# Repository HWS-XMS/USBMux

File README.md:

# USBMux

USB multiplexer for switching a USB device between two hosts, with VBUS power control.

## Hardware

- **MCU**: STM32F042F4P6 (USB CDC interface)
- **USB Mux**: FSUSB42MUX
- **VBUS Switch**: 2x TPS2051CDBV (with overcurrent/thermal protection)

KiCad design files in `hardware/`.

## Firmware

### Build

```bash
cd firmware
git submodule update --init --recursive
# Apply libopencm3 fix for STM32F042 USB bug
cd libopencm3 && patch -p1 < ../libopencm3-stm32f042-usb-fix.patch && cd ..
make -C libopencm3 TARGETS="stm32/f0" -j$(nproc)
make
```

**Note**: The patch fixes a critical bug in libopencm3's `st_usbfs_copy_from_pm()` function that causes data corruption when receiving odd-length USB packets on STM32F042. This bug has been reported to the libopencm3 project.

### Flash

```bash
make flash    # via ST-Link
make program  # via DFU mode
```

### Commands (USB CDC)

| Command | Description |
|---------|-------------|
| `SEL 0` / `SEL 1` | Select host 0 or 1 |
| `SEL?` | Query selection |
| `OE 0` / `OE 1` | Disable/enable mux |
| `OE?` | Query mux enable |
| `EN0 0` / `EN0 1` | Disable/enable VBUS channel 0 |
| `EN0?` | Query VBUS 0 |
| `EN1 0` / `EN1 1` | Disable/enable VBUS channel 1 |
| `EN1?` | Query VBUS 1 |
| `FAULT?` | Query fault flags |
| `STATUS?` | Query all states |

Responses end with `\r\n`.

## Software

Python wrapper in `software/usbmux.py`.

```python
from usbmux import USBMux

with USBMux() as mux:      # auto-detects device
    mux.sel = 0            # select host 0
    mux.oe = True          # enable mux
    mux.en0 = True         # enable VBUS 0 (raises USBMuxFaultError on fault)
    print(mux.status)
```

Requires `pyserial`:
```bash
pip install pyserial
```

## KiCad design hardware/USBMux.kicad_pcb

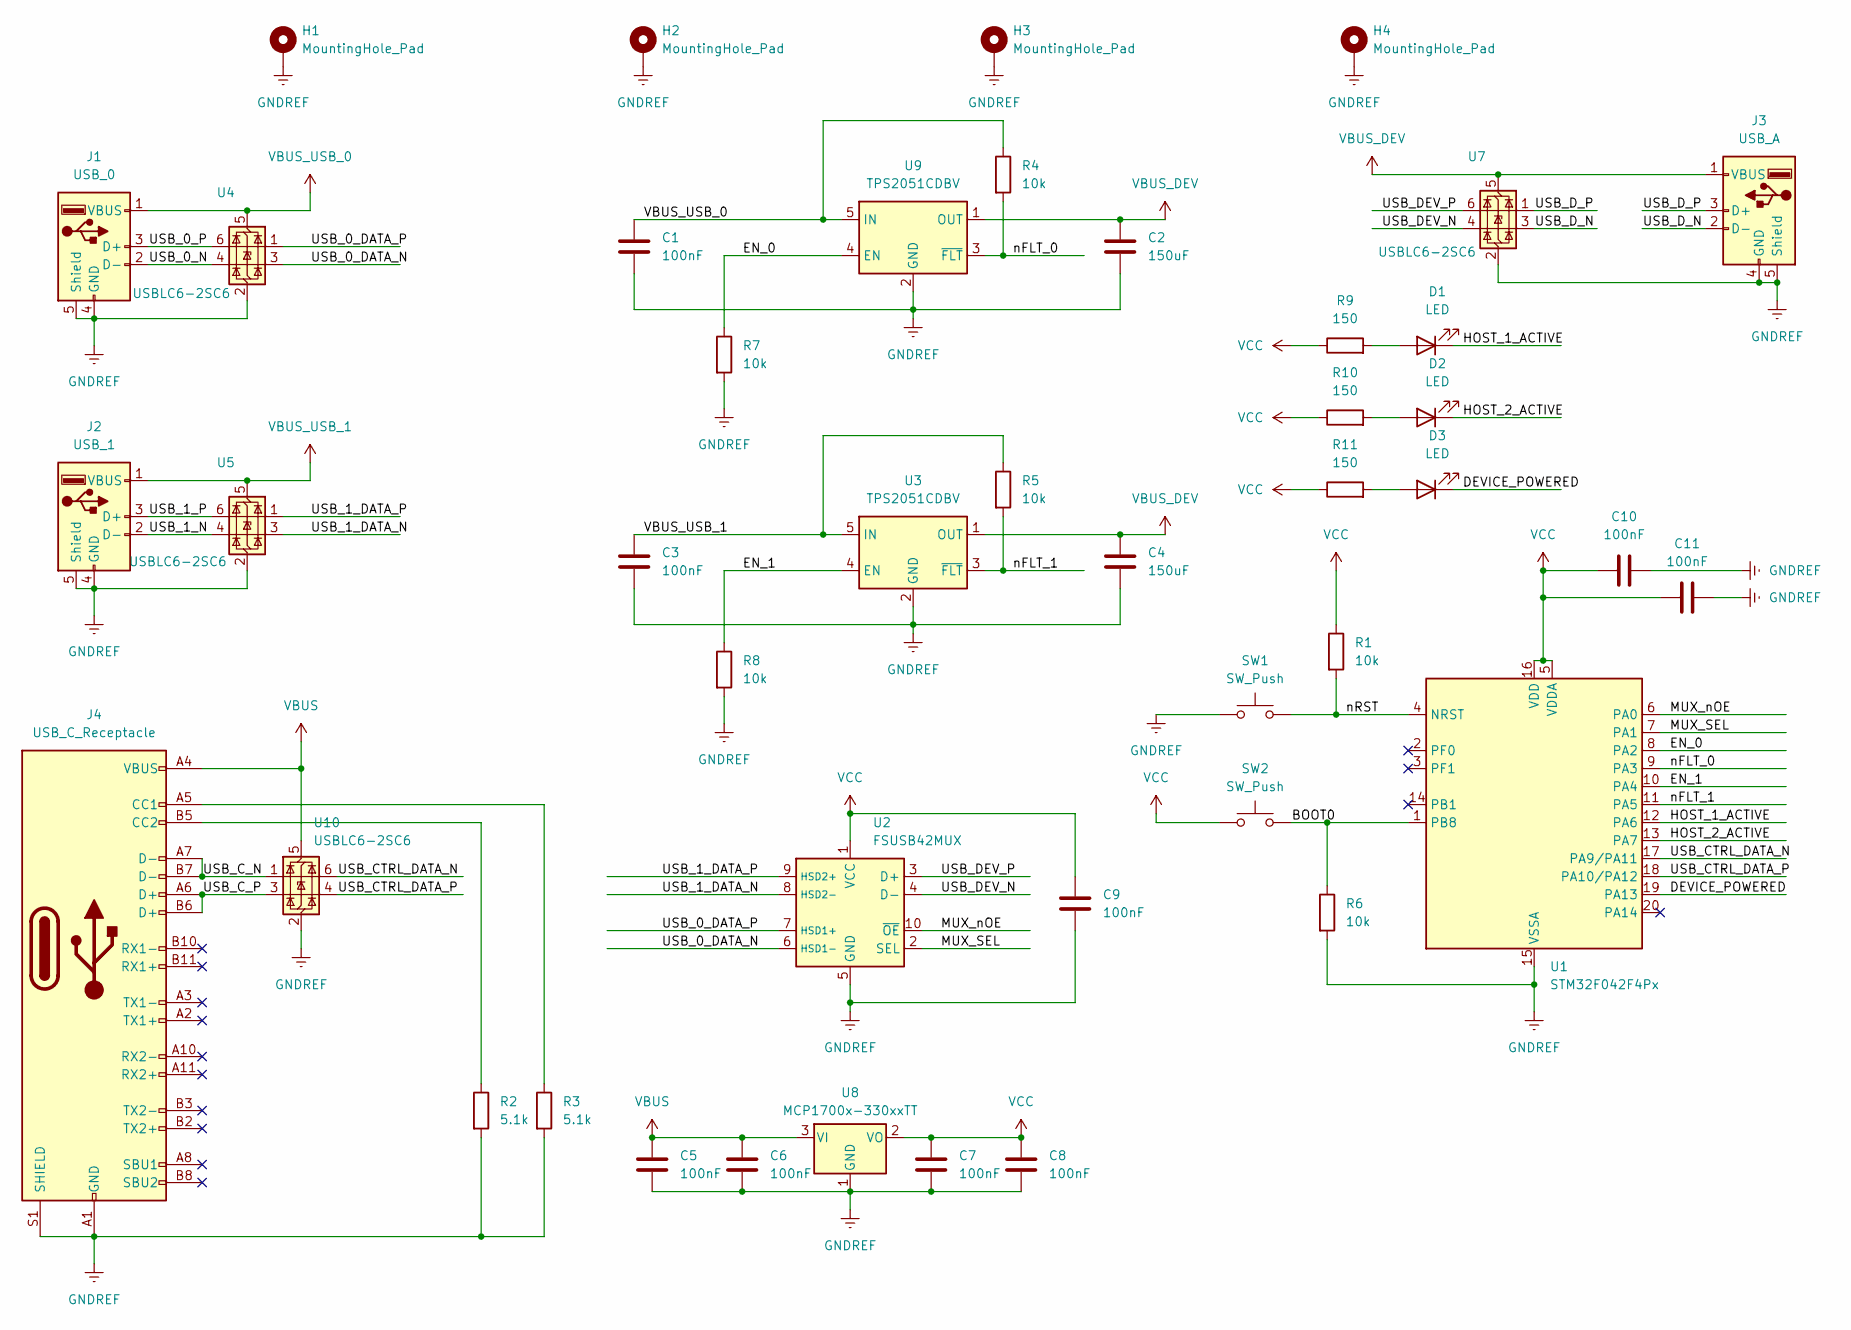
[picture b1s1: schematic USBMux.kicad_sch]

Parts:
C1, C3, C5, C6, C7, C8, C9, C10, C11: 100nF; C_0805_2012Metric_Pad1.18x1.45mm_HandSolder
C2, C4: 150uF; C_0805_2012Metric_Pad1.18x1.45mm_HandSolder
D1, D2, D3: LED; LED_0805_2012Metric_Pad1.15x1.40mm_HandSolder
H1, H2, H3, H4: MountingHole_Pad; MountingHole_3.2mm_M3_DIN965_Pad
J1: USB_0; USB_A_Receptacle_GCT_USB1046
J2: USB_1; USB_A_Receptacle_GCT_USB1046
J3: USB_A; USB_A_Receptacle_GCT_USB1046
J4: USB_C_Receptacle; USB_C_Receptacle_GCT_USB4085
R1, R4, R5, R6, R7, R8: 10k; R_0805_2012Metric_Pad1.20x1.40mm_HandSolder
R2, R3: 5.1k; R_0805_2012Metric_Pad1.20x1.40mm_HandSolder
R9, R10, R11: 150; R_0805_2012Metric_Pad1.20x1.40mm_HandSolder
SW1, SW2: SW_Push; SW_Push_1TS009xxxx-xxxx-xxxx_6x6x5mm
U1: STM32F042F4Px; TSSOP-20_4.4x6.5mm_P0.65mm
U2: FSUSB42MUX; MSOP-10_3x3mm_P0.5mm
U3, U9: TPS2051CDBV; SOT-23-5
U4, U5, U7, U10: USBLC6-2SC6; SOT-23-6
U8: MCP1700x-330xxTT; SOT-23

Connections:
/BOOT0: R6.1, SW2.2, U1.1 (PB8)
/DEVICE_POWERED: D3.1 (K), U1.19 (PA13)
/EN_0: R7.1, U1.8 (PA2), U9.4 (EN)
/EN_1: R8.1, U1.10 (PA4), U3.4 (EN)
/HOST_1_ACTIVE: D1.1 (K), U1.12 (PA6)
/HOST_2_ACTIVE: D2.1 (K), U1.13 (PA7)
/MUX_SEL: U1.7 (PA1), U2.2 (SEL)
/MUX_nOE: U1.6 (PA0), U2.10 (~OE)
/USB_0_DATA_N: U2.6 (HSD1-), U4.3 (I/O2)
/USB_0_DATA_P: U2.7 (HSD1+), U4.1 (I/O1)
/USB_0_N: J1.2 (D-), U4.4 (I/O2)
/USB_0_P: J1.3 (D+), U4.6 (I/O1)
/USB_1_DATA_N: U2.8 (HSD2-), U5.3 (I/O2)
/USB_1_DATA_P: U2.9 (HSD2+), U5.1 (I/O1)
/USB_1_N: J2.2 (D-), U5.4 (I/O2)
/USB_1_P: J2.3 (D+), U5.6 (I/O1)
/USB_CTRL_DATA_N: U1.17 (PA9/PA11), U10.6 (I/O1)
/USB_CTRL_DATA_P: U1.18 (PA10/PA12), U10.4 (I/O2)
/USB_C_N: J4.A7 (D-), J4.B7 (D-), U10.1 (I/O1)
/USB_C_P: J4.A6 (D+), J4.B6 (D+), U10.3 (I/O2)
/USB_DEV_N: U2.4 (D-), U7.4 (I/O2)
/USB_DEV_P: U2.3 (D+), U7.6 (I/O1)
/USB_D_N: J3.2 (D-), U7.3 (I/O2)
/USB_D_P: J3.3 (D+), U7.1 (I/O1)
/nFLT_0: R4.2, U1.9 (PA3), U9.3 (~FLT)
/nFLT_1: R5.2, U1.11 (PA5), U3.3 (~FLT)
/nRST: R1.2, SW1.2, U1.4 (NRST)
GNDREF: C1.2, C2.2, C3.2, C4.2, C5.2, C6.2, C7.2, C8.2, C9.2, C10.1, C11.1, H1.1, H2.1, H3.1, H4.1, J1.4 (GND), J1.5 (Shield), J2.4 (GND), J2.5 (Shield), J3.4 (GND), J3.5 (Shield), J4.A1 (GND), J4.A12 (GND), J4.B1 (GND), J4.B12 (GND), J4.S1 (SHIELD), R2.2, R3.2, R6.2, R7.2, R8.2, SW1.1, U1.15 (VSSA), U2.5 (GND), U3.2 (GND), U4.2 (GND), U5.2 (GND), U7.2 (GND), U8.1 (GND), U9.2 (GND), U10.2 (GND)
unnamed: D1.2 (A), R9.2
unnamed: D2.2 (A), R10.2
unnamed: D3.2 (A), R11.2
unnamed: J4.A5 (CC1), R3.1
unnamed: J4.B5 (CC2), R2.1
VBUS: C5.1, C6.1, J4.A4 (VBUS), J4.A9 (VBUS), J4.B4 (VBUS), J4.B9 (VBUS), U8.3 (VI), U10.5 (VBUS)
VBUS_DEV: C2.1, C4.1, J3.1 (VBUS), U3.1 (OUT), U7.5 (VBUS), U9.1 (OUT)
VBUS_USB_0: C1.1, J1.1 (VBUS), R4.1, U4.5 (VBUS), U9.5 (IN)
VBUS_USB_1: C3.1, J2.1 (VBUS), R5.1, U3.5 (IN), U5.5 (VBUS)
VCC: C7.1, C8.1, C9.1, C10.2, C11.2, R1.1, R9.1, R10.1, R11.1, SW2.1, U1.5 (VDDA), U1.16 (VDD), U2.1 (VCC), U8.2 (VO)

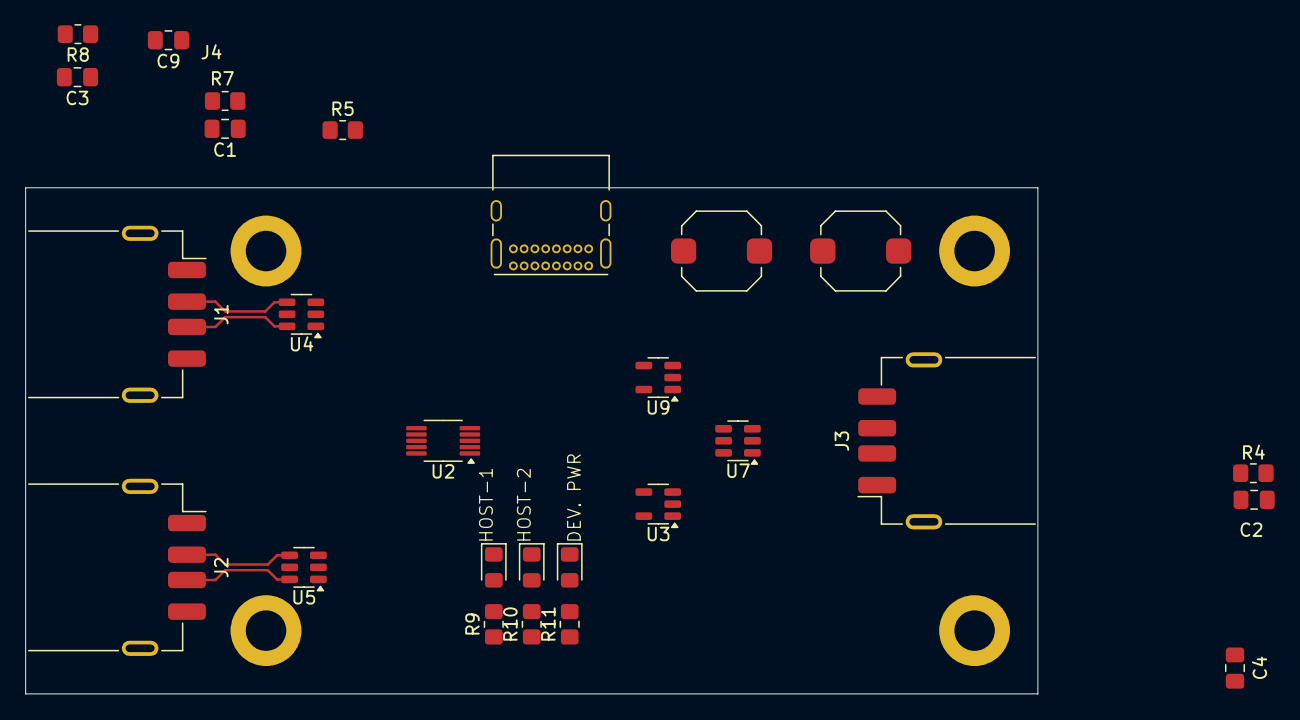
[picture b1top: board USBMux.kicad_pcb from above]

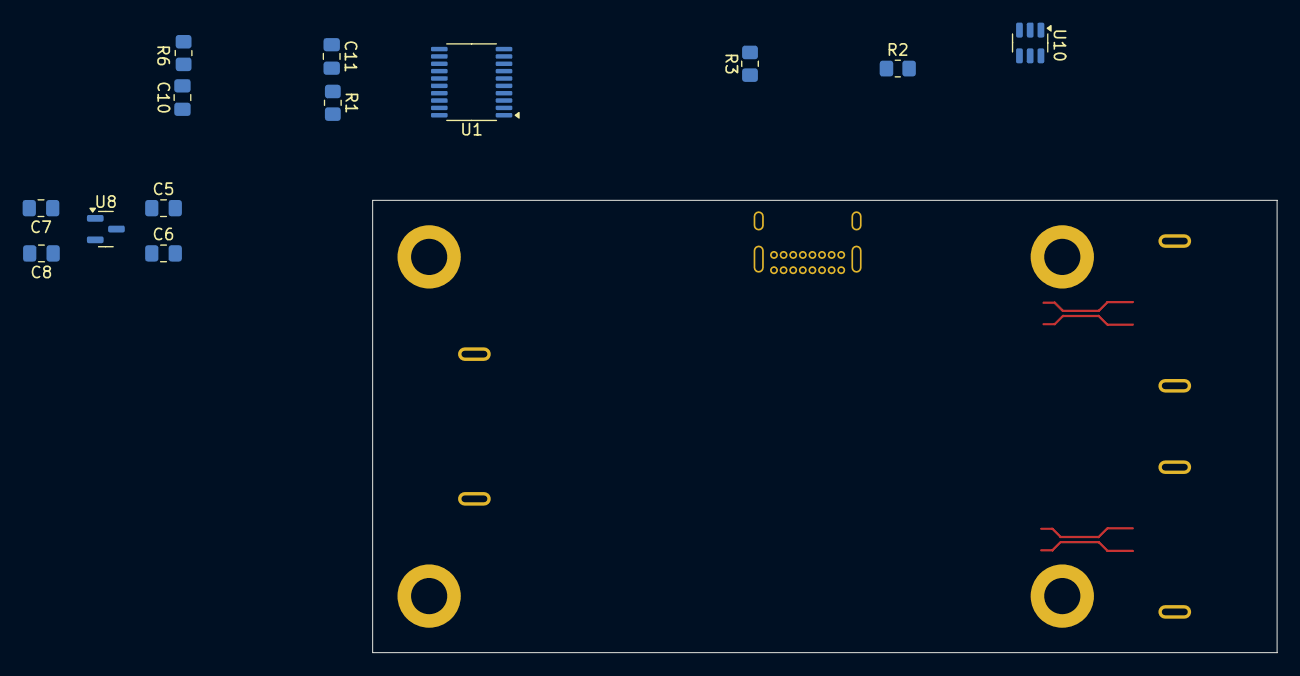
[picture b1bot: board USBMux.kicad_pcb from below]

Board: 4 copper layers, 80.0 x 40.0 mm, 44 parts (13 on the bottom side), 38 nets.

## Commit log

2025-12-04 Init
2025-12-04 Readme
2025-12-08 Testing FW on actual HW; fixing libopencm3 bug in STM USB;
2025-12-08 Fixing GPIO
2025-12-08 Creatning a proper package and assigning custom PID/VID
2025-12-11 Update PCB, fix bug in BOOT0
